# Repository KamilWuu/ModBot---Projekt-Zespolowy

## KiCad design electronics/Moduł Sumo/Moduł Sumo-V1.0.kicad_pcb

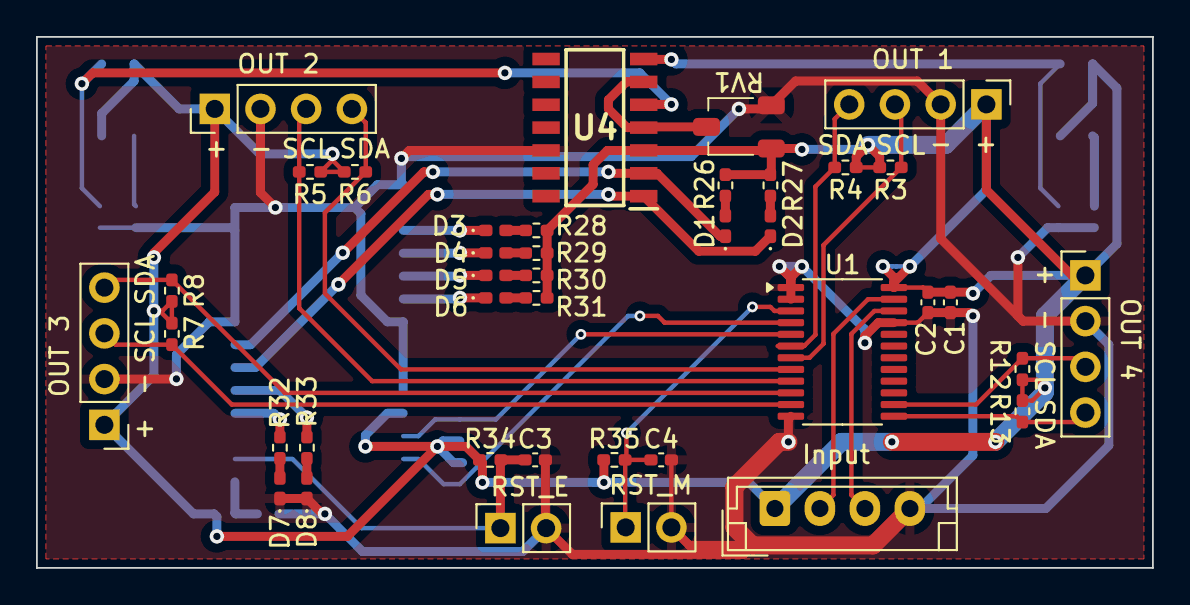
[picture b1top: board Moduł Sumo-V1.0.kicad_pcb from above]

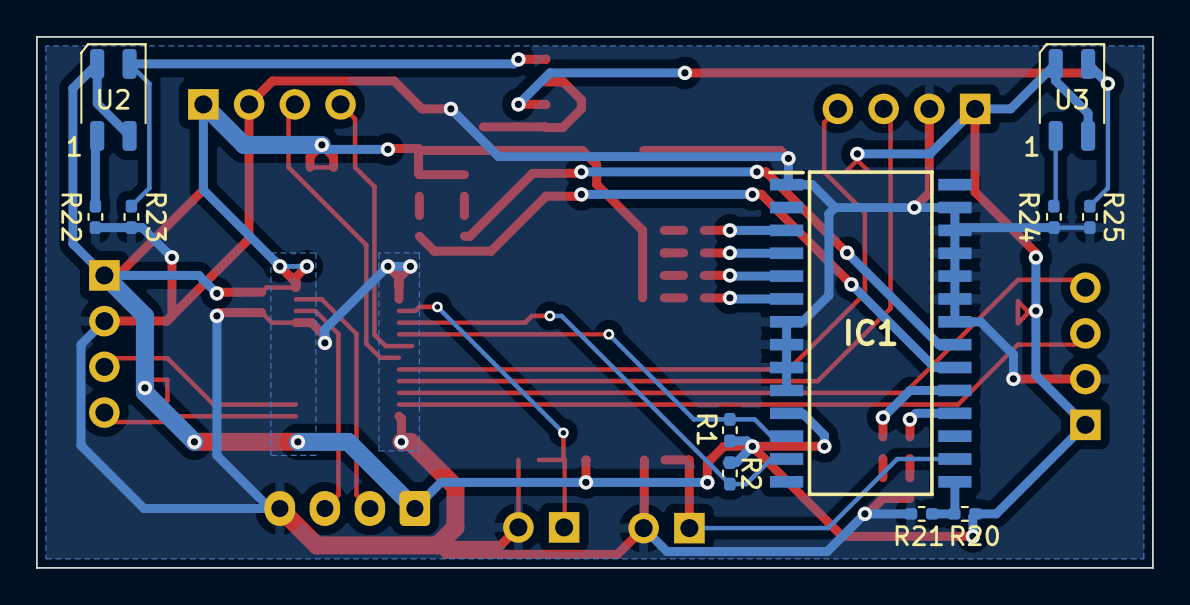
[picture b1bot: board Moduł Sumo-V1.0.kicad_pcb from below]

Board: 2 copper layers, 62.0 x 29.5 mm, 51 parts (11 on the bottom side), 38 nets.

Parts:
C1: 22uF; C_0402_1005Metric_Pad0.74x0.62mm_HandSolder
C2, C3, C4: 100nF; C_0402_1005Metric_Pad0.74x0.62mm_HandSolder
D1, D2, D3, D4, D5, D6, D7, D8: LED; LED_0402_1005Metric_Pad0.77x0.64mm_HandSolder
IC1: MCP23018-E_SO; SOIC127P1030X265-28N
J1: Input; JST_EH_B4B-EH-A_1x04_P2.50mm_Vertical
J2: OUT 1; PinHeader_1x04_P2.54mm_Vertical
J3: OUT 2; PinHeader_1x04_P2.54mm_Vertical
J4: OUT 3; PinHeader_1x04_P2.54mm_Vertical
J5: OUT 4; PinHeader_1x04_P2.54mm_Vertical
J6: RST_M; PinSocket_1x02_P2.54mm_Vertical
J7: RST_E; PinSocket_1x02_P2.54mm_Vertical
R1, R2, R3, R4, R5, R6, R7, R8, R12, R13, R34, R35: 2,2kR; R_0402_1005Metric_Pad0.72x0.64mm_HandSolder
R20: 1kR; R_0402_1005Metric_Pad0.72x0.64mm_HandSolder
R21: 15kR; R_0402_1005Metric_Pad0.72x0.64mm_HandSolder
R22, R24: 110R; R_0402_1005Metric_Pad0.72x0.64mm_HandSolder
R23, R25: 22kR; R_0402_1005Metric_Pad0.72x0.64mm_HandSolder
R26, R27, R28, R29, R30, R31, R32, R33: 330R; R_0402_1005Metric_Pad0.72x0.64mm_HandSolder
RV1: 10kR; Potencjometr 3,2x3,4
U1: TCA9548APWR; TSSOP-24_4.4x7.8mm_P0.65mm
U2, U3: ITR8307-S17-TR8; Everlight_ITR1201SR10AR
U4: LM2901; SOIC127P600X175-14N

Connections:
+3.3V: C1.1, C2.1, IC1.11 (VDD), J1.1, J2.1, J3.1, J4.1, J5.1, R1.1, R2.1, R3.1, R4.1, R5.1, R6.1, R7.1, R8.1, R12.1, R13.1, R20.1, R26.1, R27.1, R28.1, R29.1, R30.1, R31.1, R34.1, R35.1, RV1.1, U1.24 (VCC), U2.2 (A), U2.3, U3.2 (A), U3.3, U4.3 (V+)
GND: C1.2, C2.2, C3.2, C4.2, D7.1 (K), D8.1 (K), IC1.1 (VSS), IC1.7 (GPB4), IC1.8 (GPB5), IC1.9 (GPB6), IC1.10 (GPB7), IC1.22 (GPA2), IC1.23 (GPA3), IC1.24 (GPA4), IC1.25 (GPA5), IC1.26 (GPA6), IC1.27 (GPA7), J1.4, J2.2, J3.2, J4.2, J5.2, J6.2, J7.2, R21.2, R22.2, R23.2, R24.2, R25.2, RV1.3, U1.1 (A0), U1.2 (A1), U1.12 (GND), U1.21 (A2), U4.12 (V-)
GPA0: D2.1 (K), IC1.20 (GPA0), U4.1
GPA1: D1.1 (K), IC1.21 (GPA1), U4.2
GPB0: D3.1 (K), IC1.3 (GPB0)
GPB1: D4.1 (K), IC1.4 (GPB1)
GPB2: D5.1 (K), IC1.5 (GPB2)
GPB3: D6.1 (K), IC1.6 (GPB3)
INTA: IC1.19 (INTA), R33.1
INTB: IC1.18 (INTB), R32.1
IR_SENSE0: R23.1, U2.4, U4.7 (+)
IR_SENSE1: R25.1, U3.4, U4.5 (+)
unnamed: D1.2 (A), R26.2
unnamed: D2.2 (A), R27.2
unnamed: D3.2 (A), R28.2
unnamed: D4.2 (A), R29.2
unnamed: D5.2 (A), R30.2
unnamed: D6.2 (A), R31.2
unnamed: D7.2 (A), R32.2
unnamed: D8.2 (A), R33.2
unnamed: IC1.15 (ADDR), R20.2, R21.1
unnamed: R22.1, U2.1 (K)
unnamed: R24.1, U3.1 (K)
RST_E: C3.1, IC1.16 (~RESET), J7.1, R34.2
RST_M: C4.1, J6.1, R35.2, U1.3 (~RESET)
SC0: IC1.12 (SCL), R1.2, U1.5 (SC0)
SC1: J2.3, R3.2, U1.7 (SC1)
SC2: J3.3, R5.2, U1.9 (SC2)
SC3: J4.3, R7.2, U1.11 (SC3)
SC4: J5.3, R12.2, U1.14 (SC4)
SCL: J1.3, U1.22 (SCL)
SD0: IC1.13 (SDA), R2.2, U1.4 (SD0)
SD1: J2.4, R4.2, U1.6 (SD1)
SD2: J3.4, R6.2, U1.8 (SD2)
SD3: J4.4, R8.2, U1.10 (SD3)
SD4: J5.4, R13.2, U1.13 (SD4)
SDA: J1.2, U1.23 (SDA)
V_REF: RV1.2, U4.4 (-), U4.6 (-)
